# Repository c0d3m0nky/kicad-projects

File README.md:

# kicad-projects

[Wire_Pads](https://github.com/KiCad/Wire_Pads.pretty)

[digikey-kicad-library](https://github.com/Digi-Key/digikey-kicad-library)

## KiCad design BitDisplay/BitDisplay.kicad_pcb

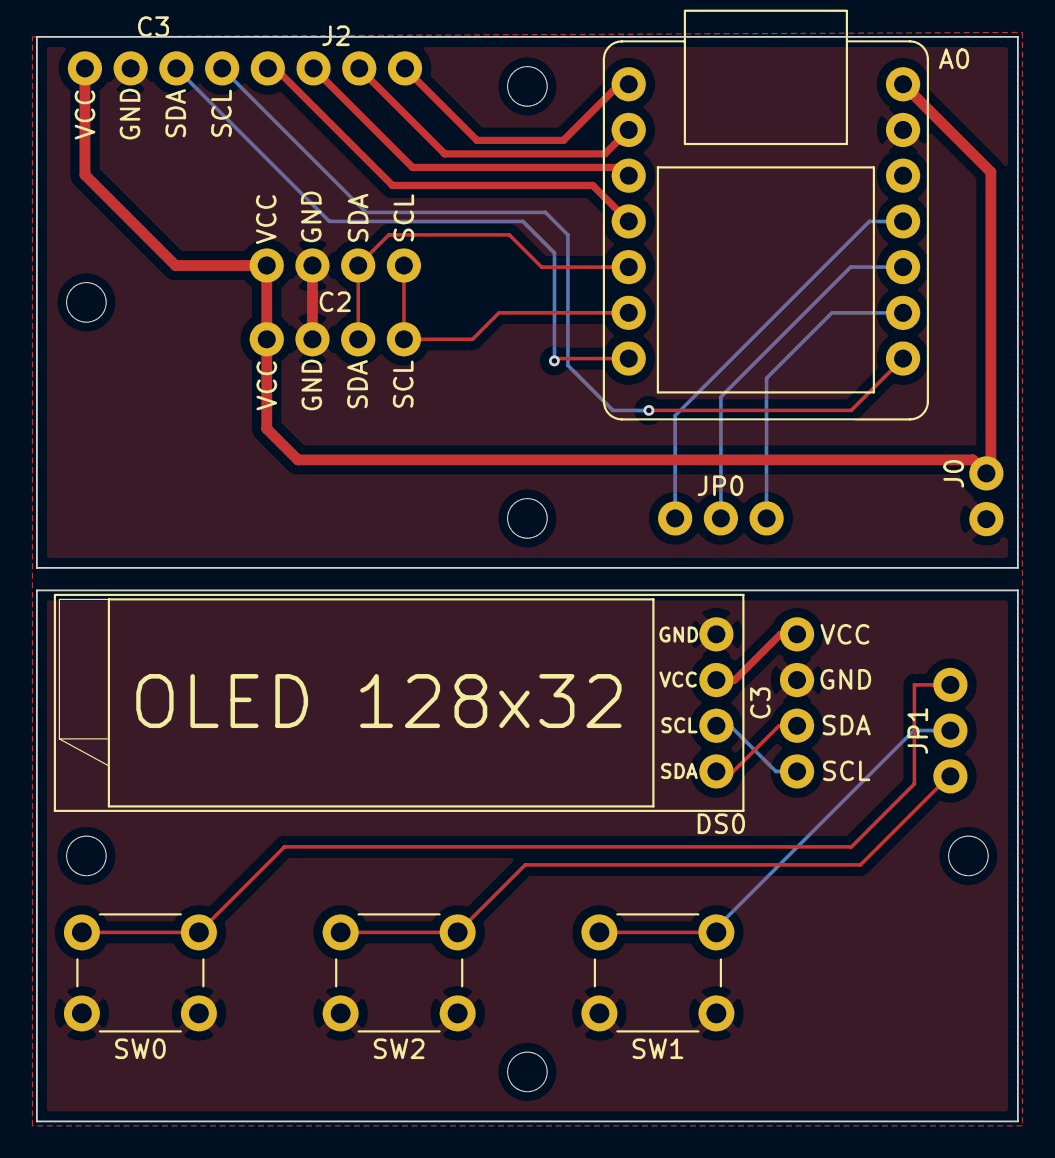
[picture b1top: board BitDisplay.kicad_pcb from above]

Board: 2 copper layers, 54.5 x 60.2 mm, 13 parts (0 on the bottom side), 13 nets.

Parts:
A0: Seed_Xiao_1.x; Seeed Xiao
C2, C2#2: I2C_BUS; I2C_Header
C3: I2C_Header
C3#2: I2C_In; I2C_Header
DS0: OLED; OLED_128x32_Doudou_SSD1306
J0: Power Hdr; SolderPinPad_Hdr_2x_1mmDrill
J2: Analog Hdr; SolderPinPad_Hdr_4xInline_1mmDrill
JP0, JP1: BtnJumper; SolderPinPad_3x_1mmDrill
SW0: Aux; SW_PUSH_6mm
SW1: Disp Mode; SW_PUSH_6mm
SW2: Input Mode; SW_PUSH_6mm

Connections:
+5V: A0.13, C2#2.1, C3.1, C3#2.1, DS0.1, J0.1
GND: A0.12, C2.2, C2#2.2, C3.2, C3#2.2, DS0.2, J0.2, SW0.1, SW1.1, SW2.1
unnamed: A0.0, J2.4
unnamed: A0.1, J2.3
unnamed: A0.2, J2.2
unnamed: A0.3, J2.1
unnamed: A0.4, C2.3, C2#2.3, C3.3, DS0.3
unnamed: A0.5, C2.4, C2#2.4, C3.4, DS0.4
unnamed: A0.6, C3#2.3
unnamed: A0.7, C3#2.4
unnamed: A0.8, JP0.3, JP1.3, SW0.2
unnamed: A0.9, JP0.2, JP1.2, SW1.2
unnamed: A0.10, JP0.1, JP1.1, SW2.2

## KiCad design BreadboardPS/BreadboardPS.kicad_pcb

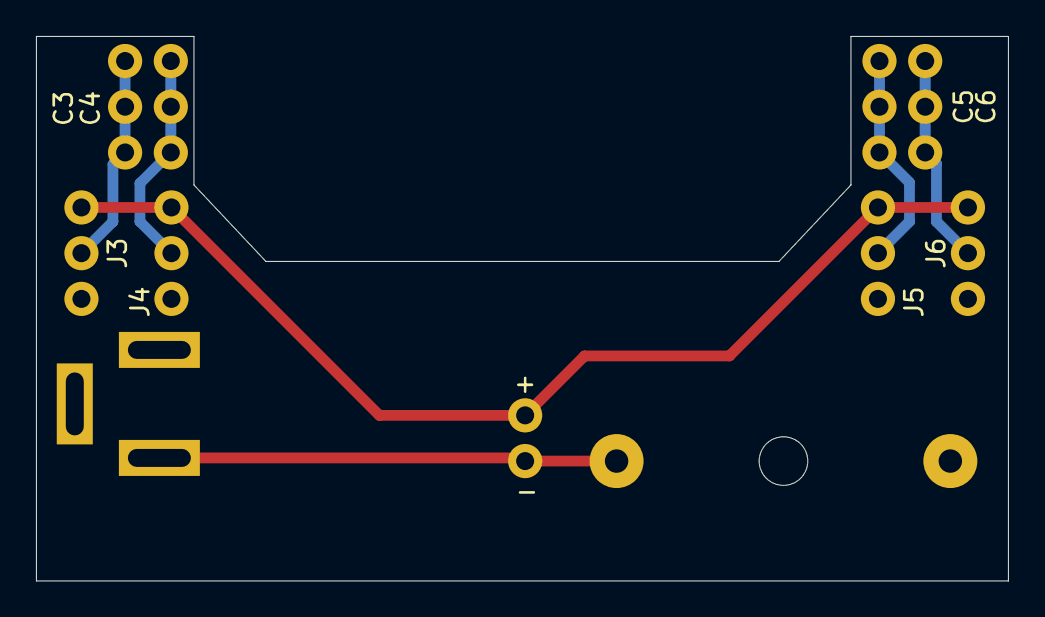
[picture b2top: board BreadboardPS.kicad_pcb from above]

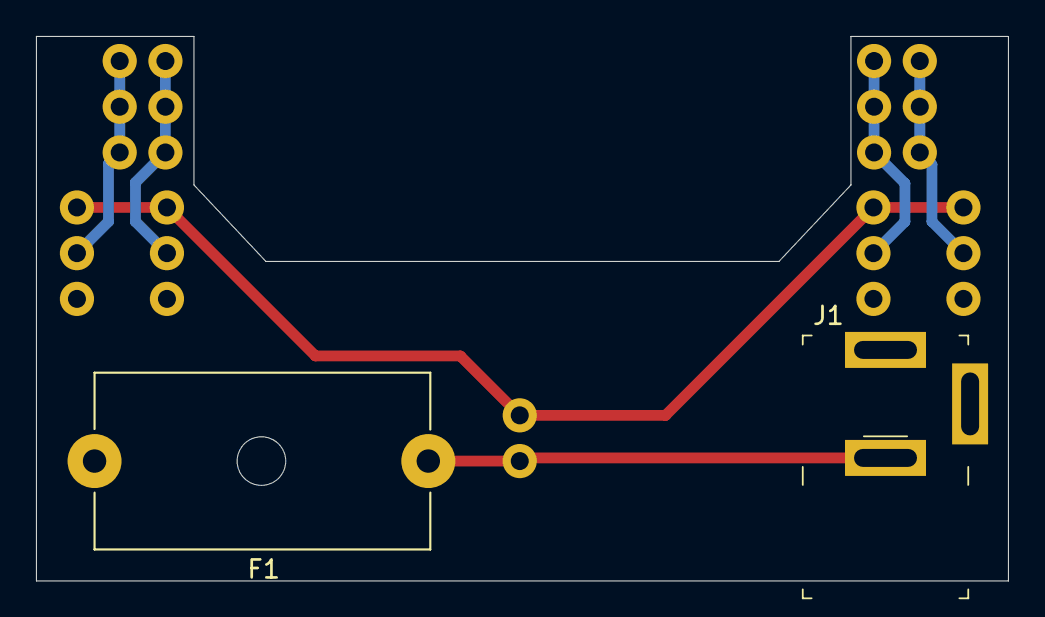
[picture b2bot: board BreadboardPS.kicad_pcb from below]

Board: 2 copper layers, 54.0 x 30.2 mm, 12 parts (2 on the bottom side), 7 nets.

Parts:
+: ConnRR; SolderPinPad_single_1mmDrill
-: ConnRR; SolderPinPad_single_1mmDrill
C3: ConnRR; SolderPinPad_3x_1mmDrill
C4: ConnRL; SolderPinPad_3x_1mmDrill
C5: ConnLR; SolderPinPad_3x_1mmDrill
C6: ConnLL; SolderPinPad_3x_1mmDrill
F1: Fuse; Fuseholder_Cylinder-0.177x0.57in_Littelfuse_02540101Z_Horiz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
J1: Barrel_Jack_MountingPin; Barrel_Jack_5.5mmODx2.1mmID_PJ-202A
J3: SinkRR; Jumper_SPDT_1mmDrill
J4: SinkRL; Jumper_SPDT_1mmDrill
J5: SinkLR; Jumper_SPDT_1mmDrill
J6: SinkLL; Jumper_SPDT_1mmDrill

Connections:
GND: F1.2, J3.1, J4.1, J5.1, J6.1
unnamed: +.1, J1.1, J3.3, J4.3, J5.3, J6.3
unnamed: -.1, F1.1, J1.2
unnamed: C3.1, J3.2
unnamed: C4.1, J4.2
unnamed: C5.1, J5.2
unnamed: C6.1, J6.2

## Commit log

2021-03-22 Init
2021-03-22 ReadMe tweak
2021-03-24 PowerSupplyV1
